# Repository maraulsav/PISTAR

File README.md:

# PISTAR
My first custom development board. I plan to made it as a part of my drone project

## 3D View
Front

Back

## PCB
My PCB is made in KiCad These are the footprints I used
- Capacitor_SMD:C_0603_1608Metric
- Capacitor_SMD:C_0402_1005Metric
- LED_SMD:LED_WS2812B_PLCC4_5.0x5.0mm_P3.2mm
- Connector_USB:USB_C_Receptacle_HRO_TYPE-C-31-M-12
- Connector_PinHeader_2.54mm:PinHeader_1x20_P2.54mm_Vertical
- Connector_PinHeader_2.54mm:PinHeader_1x03_P2.54mm_Vertical
- Resistor_SMD:R_0402_1005Metric
- Button_Switch_SMD:SW_Push_SPST_NO_Alps_SKRK
- RP2040: Package_DFN_QFN:QFN-56-1EP_7x7mm_P0.4mm_EP3.2x3.2mm
- W25Q128JVS: Package_SON:Winbond_USON-8-1EP_3x2mm_P0.5mm_EP0.2x1.6mm
- Package_TO_SOT_SMD:SOT-23
- Crystal:Crystal_SMD_3225-4Pin_3.2x2.5mm_HandSoldering

Here is my schematic:

and my PCB:

## BOM

| Name                | Purpose                               | Cost Per Item (USD) | Quantity | Total (USD) | Link | Distributor |
|---------------------|----------------------------------------|----------------------|----------|--------------|------|-------------|
| UPS Shipping        | Shipping the JLCPCB                   | 2.48                 | 1        | 2.48         | [Link](https://cart.jlcpcb.com/shopcart/cart) | JLCPCB |
| Pin Header Delivery | Delivering the pin header             | 0.83                 | 1        | 0.83         | [Link](https://www.tokopedia.com/cart/checkout?t_id=1774050616052&t_st=3&t_pp=cart&t_efo=cart&t_ef=goods_search&t_sm=&t_spt=cart) | Tokopedia |
| Pin Header 1x40 2x  | For the GPIO pins                     | 0.11                 | 1        | 0.11         | [Link](https://www.tokopedia.com/parts-shop/pin-header-male-1-x-40-pin-254mm-single-row?extParam=ivf%3Dfalse%26keyword%3Dpin+header%26search_id%3D2026032023494534ED066DF378EF117KRL%26src%3Dsearch&t_id=1774050616052&t_st=1&t_pp=search_result&t_efo=search_pure_goods_card&t_ef=goods_search&t_sm=&t_spt=search_result) | Tokopedia |
| PCB / PCBA          | PCB printing and component assembly   | 78.06                | 1        | 78.06        | [Link](https://cart.jlcpcb.com/shopcart/cart) | JLCPCB |

## Additional Thingy
Thankyou for HackClub and  KiCad for making this project possible

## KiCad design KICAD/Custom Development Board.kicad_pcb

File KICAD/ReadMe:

Hi! 
This folder contain all the KiCad files that I had. 
You can copy then modify some part of it, if you want

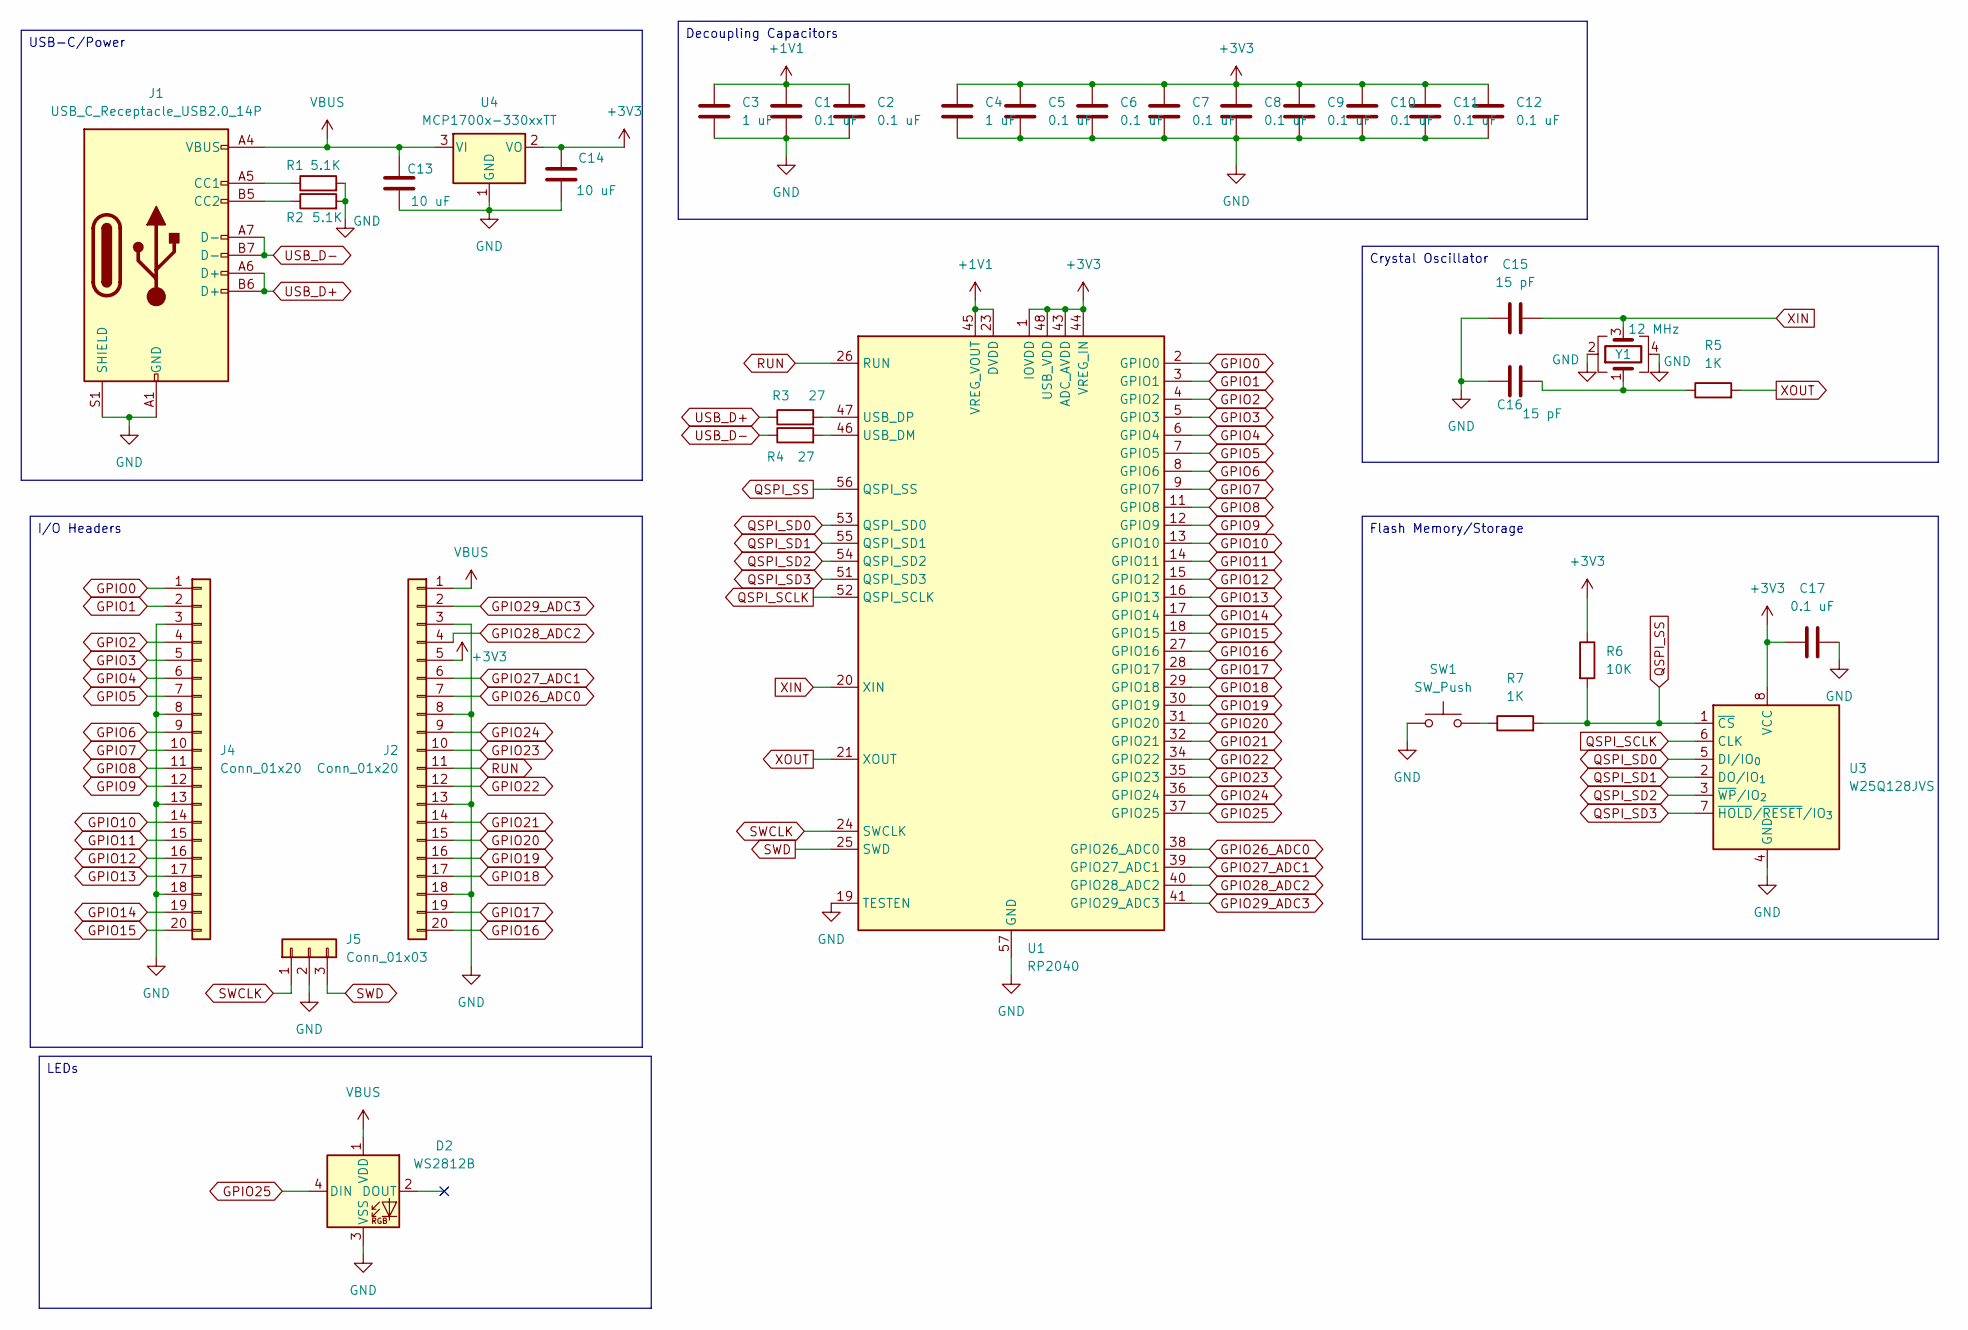
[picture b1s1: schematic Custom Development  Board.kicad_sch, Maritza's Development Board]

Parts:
C1, C2, C5, C6, C7, C8, C9, C10, C11, C12, C17: 0.1 uF; C_0402_1005Metric
C3, C4: 1 uF; C_0402_1005Metric
C13, C14: 10 uF; C_0603_1608Metric
C15, C16: 15 pF; C_0402_1005Metric
D2: WS2812B; LED_WS2812B_PLCC4_5.0x5.0mm_P3.2mm
J1: USB_C_Receptacle_USB2.0_14P; USB_C_Receptacle_HRO_TYPE-C-31-M-12
J2, J4: Conn_01x20; PinHeader_1x20_P2.54mm_Vertical
J5: Conn_01x03; PinHeader_1x03_P2.54mm_Vertical
R1, R2: 5.1K; R_0402_1005Metric
R3, R4: 27; R_0402_1005Metric
R5, R7: 1K; R_0402_1005Metric
R6: 10K; R_0402_1005Metric
SW1: SW_Push; SW_Push_SPST_NO_Alps_SKRK
U1: RP2040; QFN-56-1EP_7x7mm_P0.4mm_EP3.2x3.2mm
U3: W25Q128JVS; Winbond_USON-8-1EP_3x2mm_P0.5mm_EP0.2x1.6mm
U4: MCP1700x-330xxTT; SOT-23
Y1: 12 MHz; Crystal_SMD_3225-4Pin_3.2x2.5mm_HandSoldering

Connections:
+1V1: C1.1, C2.1, C3.1, U1.23 (DVDD), U1.45 (VREG_VOUT), U1.50 (DVDD)
+3V3: C4.1, C5.1, C6.1, C7.1, C8.1, C9.1, C10.1, C11.1, C12.1, C14.1, C17.1, J2.5, R6.1, U1.1 (IOVDD), U1.10 (IOVDD), U1.22 (IOVDD), U1.33 (IOVDD), U1.42 (IOVDD), U1.43 (ADC_AVDD), U1.44 (VREG_IN), U1.48 (USB_VDD), U1.49 (IOVDD), U3.8 (VCC), U4.2 (VO)
GND: C1.2, C2.2, C3.2, C4.2, C5.2, C6.2, C7.2, C8.2, C9.2, C10.2, C11.2, C12.2, C13.2, C14.2, C15.1, C16.1, C17.2, D2.3 (VSS), J1.A1 (GND), J1.A12 (GND), J1.B1 (GND), J1.B12 (GND), J1.S1 (SHIELD), J2.3, J2.8, J2.13, J2.18, J4.3, J4.8, J4.13, J4.18, J5.2, R1.2, R2.2, SW1.1, U1.19 (TESTEN), U1.57 (GND), U3.4 (GND), U4.1 (GND), Y1.2, Y1.4
GPIO0: J4.1, U1.2 (GPIO0)
GPIO1: J4.2, U1.3 (GPIO1)
GPIO2: J4.4, U1.4 (GPIO2)
GPIO3: J4.5, U1.5 (GPIO3)
GPIO4: J4.6, U1.6 (GPIO4)
GPIO5: J4.7, U1.7 (GPIO5)
GPIO6: J4.9, U1.8 (GPIO6)
GPIO7: J4.10, U1.9 (GPIO7)
GPIO8: J4.11, U1.11 (GPIO8)
GPIO9: J4.12, U1.12 (GPIO9)
GPIO10: J4.14, U1.13 (GPIO10)
GPIO11: J4.15, U1.14 (GPIO11)
GPIO12: J4.16, U1.15 (GPIO12)
GPIO13: J4.17, U1.16 (GPIO13)
GPIO14: J4.19, U1.17 (GPIO14)
GPIO15: J4.20, U1.18 (GPIO15)
GPIO16: J2.20, U1.27 (GPIO16)
GPIO17: J2.19, U1.28 (GPIO17)
GPIO18: J2.17, U1.29 (GPIO18)
GPIO19: J2.16, U1.30 (GPIO19)
GPIO20: J2.15, U1.31 (GPIO20)
GPIO21: J2.14, U1.32 (GPIO21)
GPIO22: J2.12, U1.34 (GPIO22)
GPIO23: J2.10, U1.35 (GPIO23)
GPIO24: J2.9, U1.36 (GPIO24)
GPIO25: D2.4 (DIN), U1.37 (GPIO25)
GPIO26_ADC0: J2.7, U1.38 (GPIO26_ADC0)
GPIO27_ADC1: J2.6, U1.39 (GPIO27_ADC1)
GPIO28_ADC2: J2.4, U1.40 (GPIO28_ADC2)
GPIO29_ADC3: J2.2, U1.41 (GPIO29_ADC3)
unnamed: C16.2, R5.1, Y1.1
unnamed: J1.A5 (CC1), R1.1
unnamed: J1.B5 (CC2), R2.1
unnamed: R7.1, SW1.2
unnamed: R4.2, U1.46 (USB_DM)
unnamed: R3.2, U1.47 (USB_DP)
QSPI_SCLK: U1.52 (QSPI_SCLK), U3.6 (CLK)
QSPI_SD0: U1.53 (QSPI_SD0), U3.5 (DI/IO_{0})
QSPI_SD1: U1.55 (QSPI_SD1), U3.2 (DO/IO_{1})
QSPI_SD2: U1.54 (QSPI_SD2), U3.3 (~WP/IO_{2})
QSPI_SD3: U1.51 (QSPI_SD3), U3.7 (~HOLD/~RESET/IO_{3})
QSPI_SS: R6.2, R7.2, U1.56 (QSPI_SS), U3.1 (~CS)
RUN: J2.11, U1.26 (RUN)
SWCLK: J5.1, U1.24 (SWCLK)
SWD: J5.3, U1.25 (SWD)
USB_D+: J1.A6 (D+), J1.B6 (D+), R3.1
USB_D-: J1.A7 (D-), J1.B7 (D-), R4.1
VBUS: C13.1, D2.1 (VDD), J1.A4 (VBUS), J1.A9 (VBUS), J1.B4 (VBUS), J1.B9 (VBUS), J2.1, U4.3 (VI)
XIN: C15.2, U1.20 (XIN), Y1.3
XOUT: R5.2, U1.21 (XOUT)

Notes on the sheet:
Decoupling Capacitors
Flash Memory/Storage
USB-C/Power
LEDs
Crystal Oscillator
I/O Headers

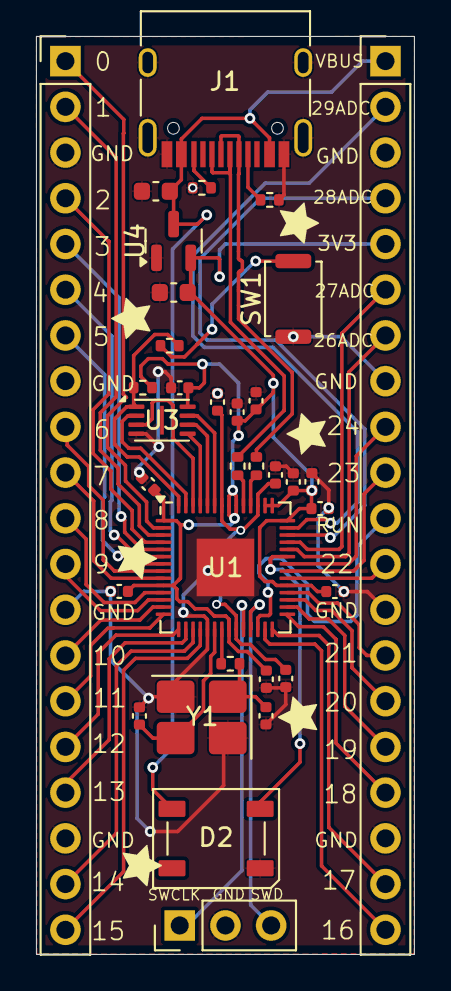
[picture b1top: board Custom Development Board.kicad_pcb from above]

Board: 2 copper layers, 21.0 x 51.0 mm, 34 parts (0 on the bottom side), 53 nets.
